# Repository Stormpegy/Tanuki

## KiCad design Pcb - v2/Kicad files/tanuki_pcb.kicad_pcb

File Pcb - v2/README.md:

# Tanuki 40% keyboard  

## PCB v2  
started to work on a full SMD redesign of the pcb but USB type-C s too wide so I've put it on hold while I figure out if I want to use mini or just not bother and use the original  
-stormpegy

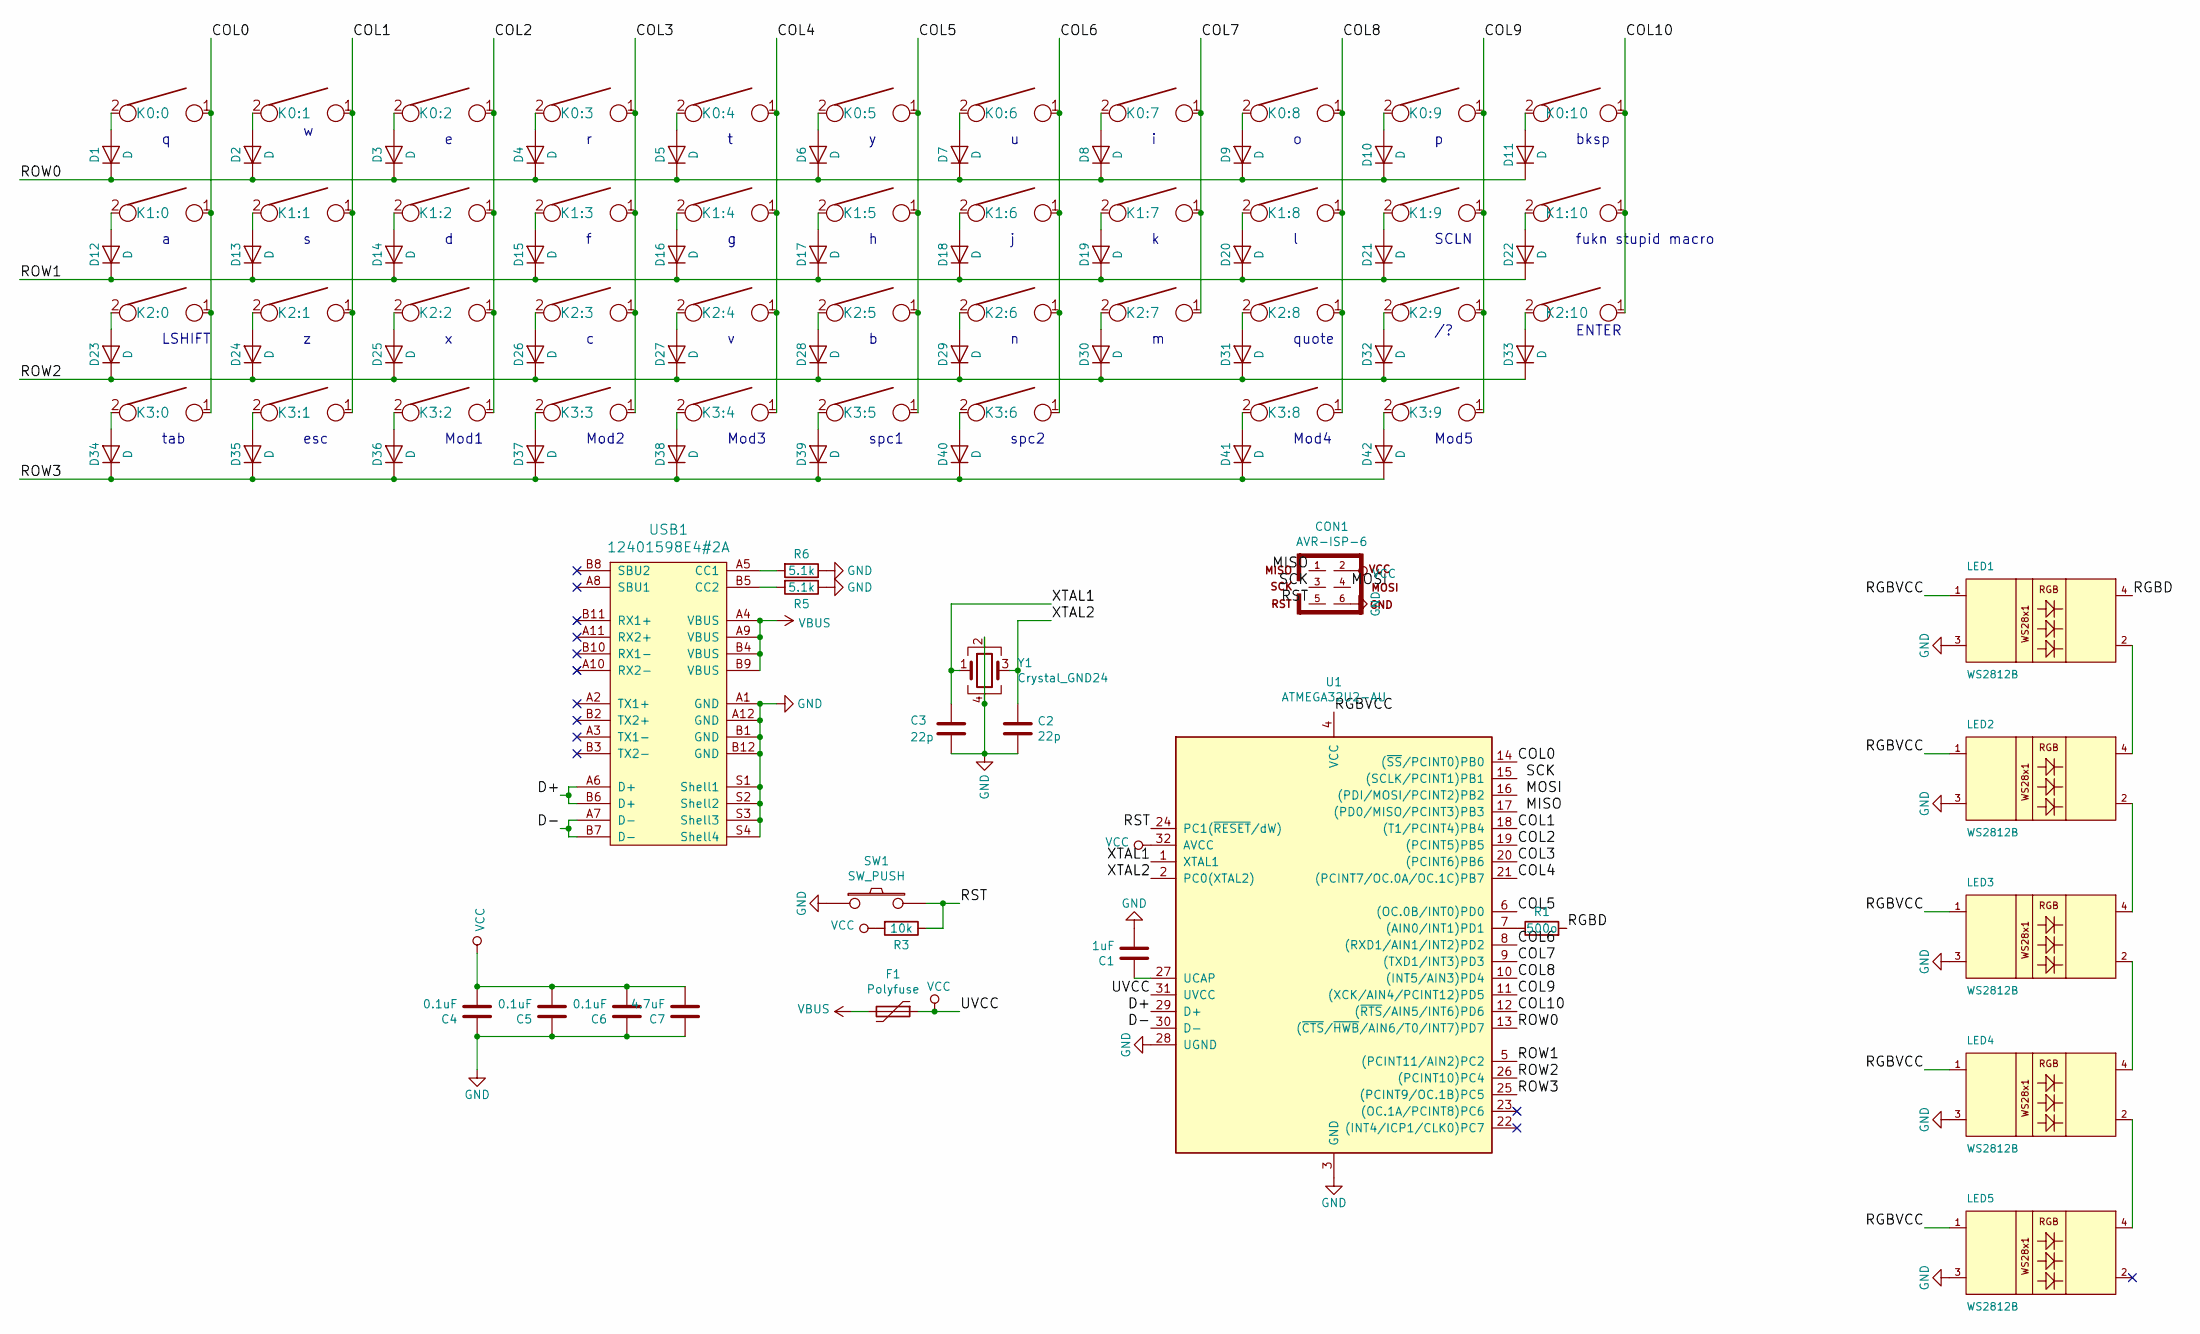
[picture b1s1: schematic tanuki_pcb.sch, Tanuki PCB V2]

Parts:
C1: 1uF; C_0805
C2, C3: 22p; C_0805
C4, C5, C6: 0.1uF; C_0805
C7: 4.7uF; C_0805
CON1: AVR-ISP-6; Reset_Pretty
D1, D2, D3, D4, D5, D6, D7, D8, D9, D10, D11, D12, D13, D14, D15, D16, D17, D18, D19, D20, D21, D22, D23, D24, D25, D26, D27, D28, D29, D30, D31, D32, D33, D34, D35, D36, D37, D38, D39, D40, D41, D42: D; D_SOD-123
F1: Polyfuse; R_1206_HandSoldering
K0:0, K0:1, K0:2, K0:3, K0:4, K0:5, K0:6, K0:7, K0:8, K0:9, K1:0, K1:1, K1:2, K1:3, K1:4, K1:5, K1:6, K1:7, K1:8, K1:9, K1:10, K2:1, K2:2, K2:3, K2:4, K2:5, K2:6, K2:7, K2:8, K2:9, K3:1, K3:3, K3:4, K3:5, K3:6, K3:8: KEYSW; MX_PCB_100H
K0:10, K2:10, K3:0, K3:2, K3:9: KEYSW; MX_PCB_125H
K2:0: KEYSW; MX_PCB_150H
LED1, LED2, LED3, LED4, LED5: WS2812B; LED_WS2812B-PLCC4
R1: 500o; R_0805
R3: 10k; R_0805
R5, R6: 5.1k; R_0805
SW1: SW_PUSH; TACTILE_SWITCH_SMD_6.0X3.5MM
U1: ATMEGA32U2-AU; TQFP-32_7x7mm_Pitch0.8mm
USB1: 12401598E4#2A; USB_C_GCT_USB4085
Y1: Crystal_GND24; Crystal_SMD_3225-4pin_3.2x2.5mm

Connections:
/COL0: K0:0.1, K1:0.1, K2:0.1, K3:0.1, U1.14 ((~SS~/PCINT0)PB0)
/COL1: K0:1.1, K1:1.1, K2:1.1, K3:1.1, U1.18 ((T1/PCINT4)PB4)
/COL2: K0:2.1, K1:2.1, K2:2.1, K3:2.1, U1.19 ((PCINT5)PB5)
/COL3: K0:3.1, K1:3.1, K2:3.1, K3:3.1, U1.20 ((PCINT6)PB6)
/COL4: K0:4.1, K1:4.1, K2:4.1, K3:4.1, U1.21 ((PCINT7/OC.0A/OC.1C)PB7)
/COL5: K0:5.1, K1:5.1, K2:5.1, K3:5.1, U1.6 ((OC.0B/INT0)PD0)
/COL6: K0:6.1, K1:6.1, K2:6.1, K3:6.1, U1.8 ((RXD1/AIN1/INT2)PD2)
/COL7: K0:7.1, K1:7.1, K2:7.1, U1.9 ((TXD1/INT3)PD3)
/COL8: K0:8.1, K1:8.1, K2:8.1, K3:8.1, U1.10 ((INT5/AIN3)PD4)
/COL9: K0:9.1, K1:9.1, K2:9.1, K3:9.1, U1.11 ((XCK/AIN4/PCINT12)PD5)
/COL10: K0:10.1, K1:10.1, K2:10.1, U1.12 ((~RTS~/AIN5/INT6)PD6)
/D+: U1.29 (D+), USB1.A6 (D+), USB1.B6 (D+)
/D-: U1.30 (D-), USB1.A7 (D-), USB1.B7 (D-)
/MISO: CON1.1
/MOSI: CON1.4
/RGBD: LED1.4 (DI), R1.2
/RGBVCC: LED1.1 (VDD), LED2.1 (VDD), LED3.1 (VDD), LED4.1 (VDD), LED5.1 (VDD), U1.4 (VCC)
/ROW0: D1.1 (K), D2.1 (K), D3.1 (K), D4.1 (K), D5.1 (K), D6.1 (K), D7.1 (K), D8.1 (K), D9.1 (K), D10.1 (K), D11.1 (K), U1.13 ((~CTS~/~HWB~/AIN6/T0/INT7)PD7)
/ROW1: D12.1 (K), D13.1 (K), D14.1 (K), D15.1 (K), D16.1 (K), D17.1 (K), D18.1 (K), D19.1 (K), D20.1 (K), D21.1 (K), D22.1 (K), U1.5 ((PCINT11/AIN2)PC2)
/ROW2: D23.1 (K), D24.1 (K), D25.1 (K), D26.1 (K), D27.1 (K), D28.1 (K), D29.1 (K), D30.1 (K), D31.1 (K), D32.1 (K), D33.1 (K), U1.26 ((PCINT10)PC4)
/ROW3: D34.1 (K), D35.1 (K), D36.1 (K), D37.1 (K), D38.1 (K), D39.1 (K), D40.1 (K), D41.1 (K), D42.1 (K), U1.25 ((PCINT9/OC.1B)PC5)
/SCK: CON1.3
/XTAL1: C3.1, U1.1 (XTAL1), Y1.1
/XTAL2: C2.1, U1.2 (PC0(XTAL2)), Y1.3
unnamed: C1.1, U1.27 (UCAP)
unnamed: D1.2 (A), K0:0.2
unnamed: D2.2 (A), K0:1.2
unnamed: D3.2 (A), K0:2.2
unnamed: D4.2 (A), K0:3.2
unnamed: D5.2 (A), K0:4.2
unnamed: D6.2 (A), K0:5.2
unnamed: D7.2 (A), K0:6.2
unnamed: D8.2 (A), K0:7.2
unnamed: D9.2 (A), K0:8.2
unnamed: D10.2 (A), K0:9.2
unnamed: D11.2 (A), K0:10.2
unnamed: D12.2 (A), K1:0.2
unnamed: D13.2 (A), K1:1.2
unnamed: D14.2 (A), K1:2.2
unnamed: D15.2 (A), K1:3.2
unnamed: D16.2 (A), K1:4.2
unnamed: D17.2 (A), K1:5.2
unnamed: D18.2 (A), K1:6.2
unnamed: D19.2 (A), K1:7.2
unnamed: D20.2 (A), K1:8.2
unnamed: D21.2 (A), K1:9.2
unnamed: D22.2 (A), K1:10.2
unnamed: D23.2 (A), K2:0.2
unnamed: D24.2 (A), K2:1.2
unnamed: D25.2 (A), K2:2.2
unnamed: D26.2 (A), K2:3.2
unnamed: D27.2 (A), K2:4.2
unnamed: D28.2 (A), K2:5.2
unnamed: D29.2 (A), K2:6.2
unnamed: D30.2 (A), K2:7.2
unnamed: D31.2 (A), K2:8.2
unnamed: D32.2 (A), K2:9.2
unnamed: D33.2 (A), K2:10.2
unnamed: D34.2 (A), K3:0.2
unnamed: D35.2 (A), K3:1.2
unnamed: D36.2 (A), K3:2.2
unnamed: D37.2 (A), K3:3.2
unnamed: D38.2 (A), K3:4.2
unnamed: D39.2 (A), K3:5.2
unnamed: D40.2 (A), K3:6.2
unnamed: D41.2 (A), K3:8.2
unnamed: D42.2 (A), K3:9.2
unnamed: LED1.2 (DO), LED2.4 (DI)
unnamed: LED2.2 (DO), LED3.4 (DI)
unnamed: LED3.2 (DO), LED4.4 (DI)
unnamed: LED4.2 (DO), LED5.4 (DI)
unnamed: R1.1, U1.7 ((AIN0/INT1)PD1)
unnamed: R5.2, USB1.B5 (CC2)
unnamed: R6.2, USB1.A5 (CC1)
VBUS: F1.2, USB1.A4 (VBUS), USB1.A9 (VBUS), USB1.B4 (VBUS), USB1.B9 (VBUS)
VCC: C4.2, C5.2, C6.2, C7.2, CON1.2, F1.1, R3.2, U1.31 (UVCC), U1.32 (AVCC)

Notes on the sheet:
tab
esc
Mod1
Mod2
Mod3
spc1
spc2
Mod4
Mod5
quote
LSHIFT
ENTER
SCLN
bksp
fukn stupid macro

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
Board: 2 copper layers, 108 parts (7 on the bottom side), 75 nets, no tracks yet.

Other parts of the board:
J1: USB_mini_micro_B; 54819-0519fix2
SW1#2: SW_PUSH; TACTILE_SWITCH_SMD_6.0X3.5MM

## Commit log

2020-05-22 blegh
